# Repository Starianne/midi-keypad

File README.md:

# midi-keypad
making a midi-keyboard using guide for hackclub half life week 3, I made it with custom footprints for the touch pads which are star shaped! <br/>
 <br/>

Features:
 - Copper pads with a custom footprint
 - 3 SK6812 MINI-E Neopixels LEDs
 - 3 keys to press as buttons
 - an esp32 s3 for all of its computing needs
<br/>
<br/>
Some more previews: <br/>
 <br/>
 <br/>

Planning the shape of the keys: <br/>
 <br/>

Schematic: <br/>

PCB routing: <br/>

BOM:

| Item | Qty | Supplier | Cost/item | Total Cost | link |
| --- | --- | --- | --- | --- | --- |
| Seeed Studio XIAO for ESP32-C3 | 1 | Aliexpress | $6.50 | $6.50 | https://www.aliexpress.com/item/1005008791664713.html?spm=a2g0o.cart.0.0.3bfa38daOnQ4bx&mp=1&pdp_npi=6%40dis%21GBP%21GBP+8.89%21GBP+4.88%21%21GBP+4.88%21%21%21%400b0fe08917932243795896854e0e53%2112000046678458240%21ct%21UK%218523359394%21%211%210%21 |
| Keys | 1 | Aliexpress | $7.41 | $7.41 | https://www.aliexpress.com/item/1005008651091078.html?spm=a2g0o.productlist.main.5.402c3c5fYHZdhM&algo_pvid=d2d84156-27e0-4c4d-8a80-7139199297f4&algo_exp_id=d2d84156-27e0-4c4d-8a80-7139199297f4-4&pdp_ext_f=%7B%22order%22%3A%22521%22%2C%22eval%22%3A%221%22%2C%22fromPage%22%3A%22search%22%7D&pdp_npi=6%40dis%21GBP%215.63%214.73%21%21%2148.48%2140.74%21%402103956a17932245240504105e1160%2112000046099032296%21sea%21UK%218523359394%21X%211%210%21n_tag%3A-29911%3Bd%3A39751746%3Bm03_new_user%3A-29895%3BpisId%3A5000000219054895&curPageLogUid=eJGoz3iKfXLM&utparam-url=scene%3Asearch%7Cquery_from%3A%7Cx_object_id%3A1005008651091078%7C_p_origin_prod%3A |
| SK6812 MINI-E Neopixels | 1 | Aliexpress | $2.12 | $2.12 | https://www.aliexpress.com/item/1005005193716172.html?spm=a2g0o.detail.0.0.7bd6kUr3kUr3pl&mp=1&pdp_npi=6%40dis%21GBP%21GBP+1.59%21GBP+1.59%21%21GBP+1.15%21%21%21%4021038a9c17932252930356037e0fb6%2112000032072424633%21ct%21UK%218523359394%21%211%210%21 |
| PCB | 1 | Aliexpress | $10.80 | $10.80 | https://cart.jlcpcb.com/quote?rand=0.41988905325264503 |
| Estimated total shipping | 1 ||| $6.46 |
| Estimated |||| $33.29 |

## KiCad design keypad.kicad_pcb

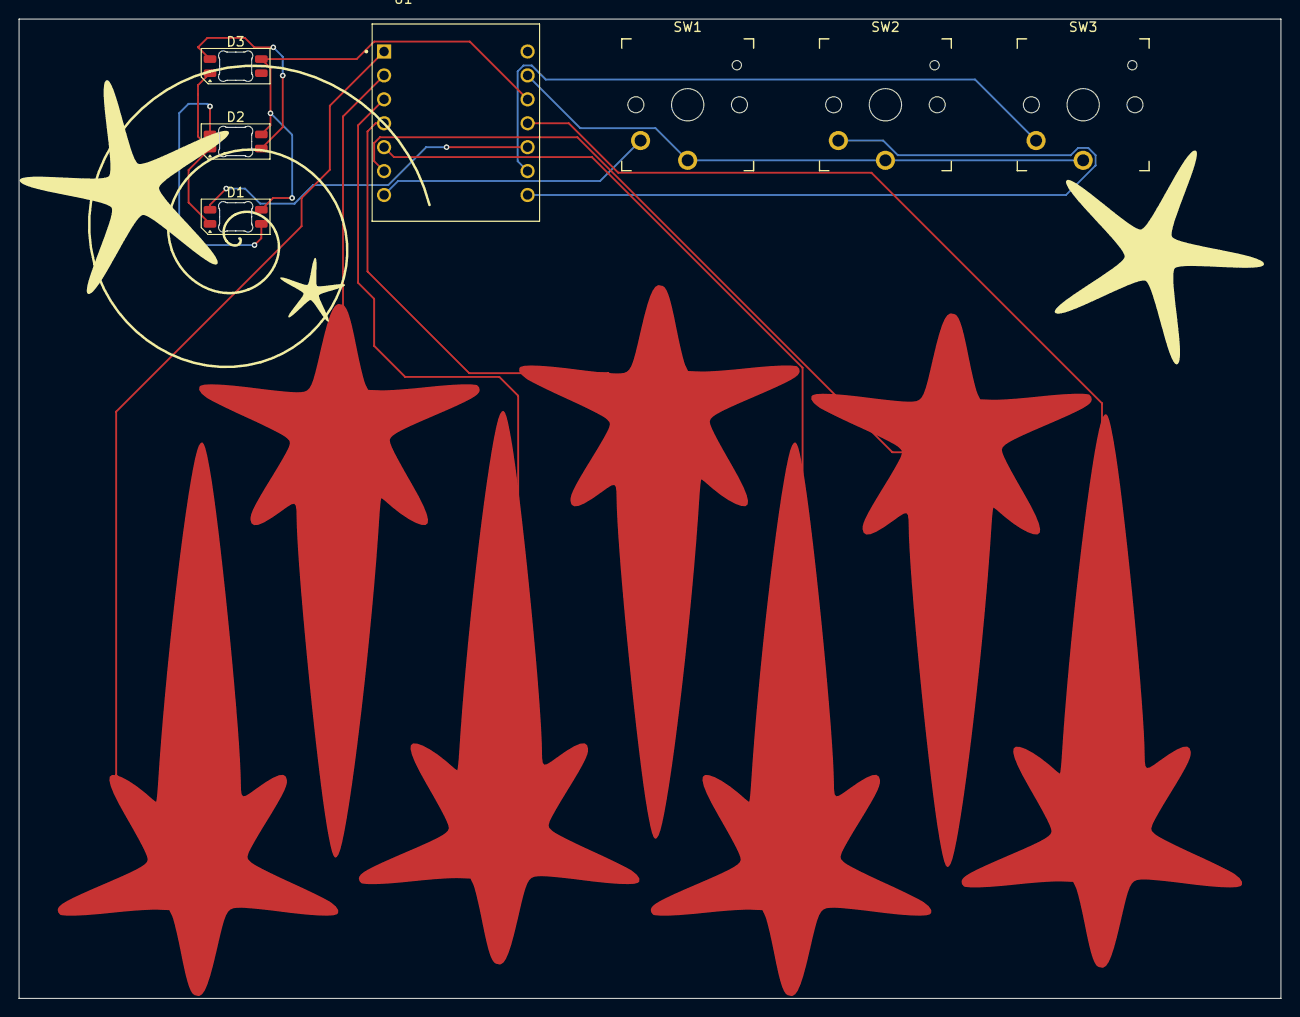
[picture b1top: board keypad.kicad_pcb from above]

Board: 2 copper layers, 134.0 x 104.0 mm, 8 parts (0 on the bottom side), 9 nets.

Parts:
D1, D2, D3: SK6812MINI-E; LED_SK6812MINI-E_3.2x2.8mm_P1.5mm_ReverseMount
J1: Capacitive touch buttons; keypadb
SW1, SW2, SW3: SW_Push; Kailh Choc Low-Profile Switches
U1: XIAO-ESP32-S3; XIAO ESP32-S3

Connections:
+3.3V: D1.3 (VDD), D2.3 (VDD), D3.3 (VDD), U1.12 (3V3)
/LED: D1.2 (DIN), U1.10 (D9/GPIO8)
/SWITCH1: SW1.2, U1.7 (D6/GPIO43)
/SWITCH2: SW2.2, U1.8 (D7/GPIO44)
/SWITCH3: SW3.2, U1.9 (D8/GPIO7)
/TOUCH2: J1.2, U1.2 (D1/GPIO2)
GND: D1.1 (VSS), D2.1 (VSS), D3.1 (VSS), SW1.1, SW2.1, SW3.1, U1.13 (GND)
unnamed: D1.4 (DOUT), D2.2 (DIN)
unnamed: D2.4 (DOUT), D3.2 (DIN)

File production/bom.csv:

Designator,Footprint,Quantity,Value,LCSC Part #
"_6, _5, _4, _3, _2, ",,6,,
"D1, D2, D3",LED_SK6812MINI-E_3.2x2.8mm_P1.5mm_ReverseMount,3,SK6812MINI-E,
J1,keypadb,1,Capacitive touch buttons,
"SW1, SW2, SW3",Kailh Choc Low-Profile Switches,3,SW_Push,
U1,XIAO ESP32-S3,1,XIAO-ESP32-S3,
